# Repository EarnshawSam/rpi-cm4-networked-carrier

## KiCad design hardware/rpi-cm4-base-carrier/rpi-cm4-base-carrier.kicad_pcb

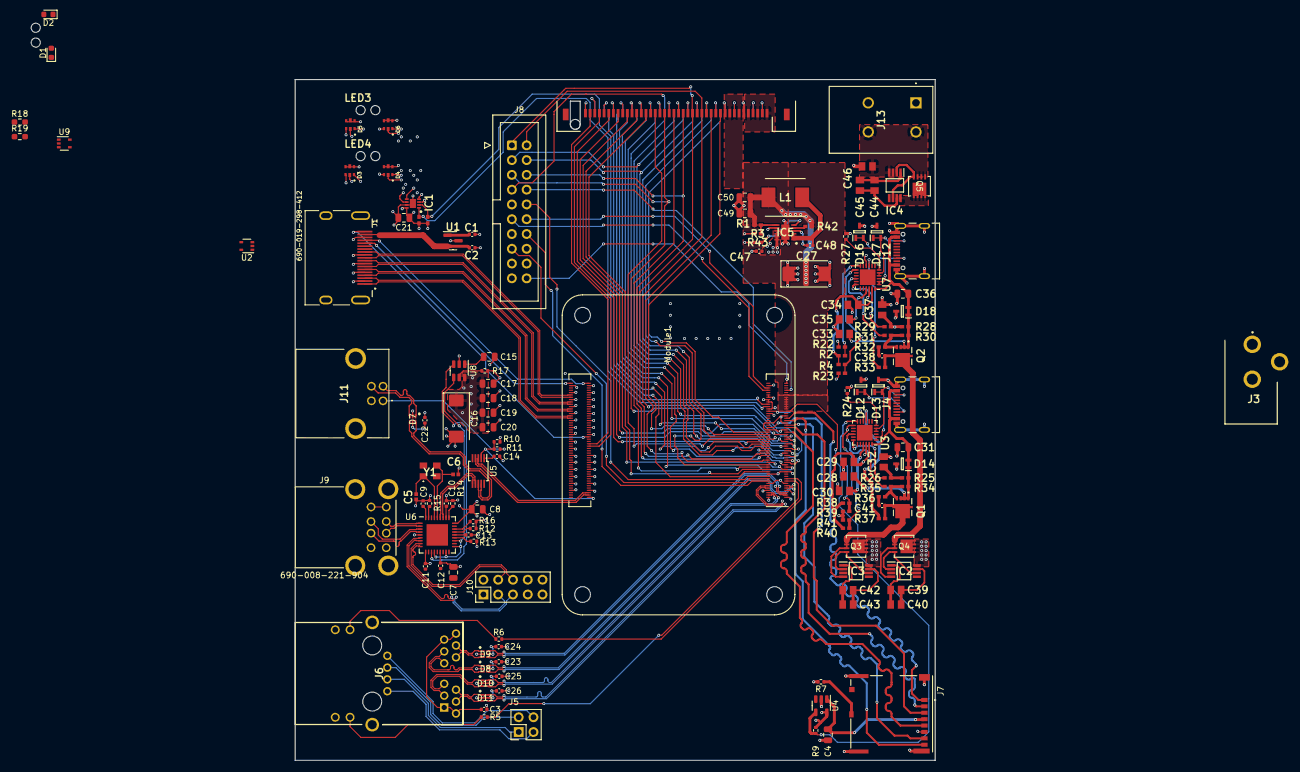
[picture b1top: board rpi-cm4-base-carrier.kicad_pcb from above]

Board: 4 copper layers, 110.0 x 117.0 mm, 148 parts (1 on the bottom side), 168 nets.

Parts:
C1, C2, C3, C9, C10, C11, C12, C13, C14, C22, C23, C24, C25, C26, C38, C41, C47, C48: 100n; C_0402_1005Metric
C4, C7, C8, C15, C17, C18, C19, C20, C21, C31, C36, C49, C50: 10u; C_0805_2012Metric
C5, C6: 8pf; CAPC1005X56N
C16, C27: 100uF; CP_EIA-7343-31_Kemet-D
C28, C29, C30, C32, C33, C34, C35, C37, C39, C40, C42, C43, C44, C45, C46: 1u; RESC2012X140N
D1: LED Green; LED_0603_1608Metric
D2: LED Red; LED_0603_1608Metric
D3, D4, D5, D6: 19-337C_RSBHGHC-A88_4T; LED_19-337C_RSBHGHC-A88_4T
D7, D8, D9, D10, D11: USBULC6-2M6; SON50P100X145X60-6N-D
D12, D13, D14, D16, D17, D18: ESDA25W; SOT65P210X110-3N
IC1: KTD2052BEVAA-TR; SON50P200X200X58-9N
IC2, IC3, IC4: LM74610QDGKRQ1; SOP65P490X110-8N
IC5: LMR51450FNDRRR; SON50P300X300X80-13N-D
J1: 690-019-298-412; EDAC 690-019-298-412
J2: ERM8-040-01-X-D-EM2-L-XX; SAMTEC_ERM8-040-01-X-D-EM2-L-XX
J3: PJ-102BH; PJ-102AH
J4, J12: USB4105-GF-A; GCT_USB4105-GF-A
J5: THD-02-R; PinHeader_2x02_P2.54mm_Vertical
J6: JT4-1202HL; JT41202HL
J7: Micro_SD_Card_Det; SDCARD_MOLEX_503398-1892
J8: Conn_02x10_Odd_Even; IDC-Header_2x10_P2.54mm_Vertical
J9: 690-008-221-904; MOLEX_USB_67298-4090
J10: Conn_02x05_Odd_Even; PinHeader_2x05_P2.54mm_Vertical
J11: XM7B-0442; XM7B0442
J13: 1190297
L1: IHLP2525EZER2R2M01-2.2uH; INDPM6965X500N
LED1, LED2, LED3, LED4: 515-1114F
Module1: ComputeModule4-CM4; Raspberry-Pi-4-Compute-Module
Q1, Q2: STL6P3LLH6; TRANS_STL6P3LLH6
Q3, Q4, Q5: STL11N3LLH6; POWERFLAT_3P3X3P3_STM
R1, R30, R34, R42: 100K; RESC1005X40N
R2, R4, R38, R41: NF; RESC1005X40N
R3: 19K1; RESC1005X40N
R5, R6: 470R; R_0402_1005Metric
R7: nf; R_0402_1005Metric
R9, R15, R24, R27: 12K 1%; R_0402_1005Metric
R10, R11: 2.2K 1%; R_0402_1005Metric
R12, R13, R14, R16: 36K 1%; R_0402_1005Metric
R17: 15K 1%; R_0402_1005Metric
R18, R19: 1k; R_0603_1608Metric_Pad0.98x0.95mm_HandSolder
R20, R21: 4K7; RESC1005X37N
R22, R23, R31, R35, R39, R40: 22K; RESC1005X40N
R25, R28: 470R; RESC1005X40N
R26, R29, R33, R37: 1k; RESC1005X37N
R32, R36: 100R; RESC1005X40N
R43: 13K3; RESC1005X40N
U1: RT9742SNGV; SOT-23
U2, U9: 74LVC1G07SE-7; SOT-353_SC-70-5
U3, U7: STUSB4500QTR; QFN-24-1EP_4x4mm_P0.5mm_EP2.7x2.7mm
U4: RT9742GGJ5; SOT-23-5
U5: FSUSB42MUX; MSOP-10_3x3mm_P0.5mm
U6: USB2514B-I/M2; QFN-36-1EP_6x6mm_P0.5mm_EP3.7x3.7mm
U8: AP22653W6; SOT-23-6
Y1: CX3225CA24000D0HSSCC

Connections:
+1V8: Module1.88 (+1.8v_(Output)), Module1.90 (+1.8v_(Output))
+3V3: C7.1, C8.1, C9.1, C10.1, C11.1, C12.1, C13.1, C14.1, C21.1, D1.2 (A), D2.2 (A), IC1.8 (VIN), J2.63, J2.67, J6.18 (A_YELLOW), J6.20 (A_GREEN), Module1.78 (GPIO_VREF(1.8v/3.3v_Input)), Module1.84 (+3.3v_(Output)), Module1.86 (+3.3v_(Output)), R7.1, R9.1, R20.2, R21.2, U4.5 (IN), U5.1 (VCC), U6.5 (VDDA33), U6.10 (VDDA33), U6.15 (VDD33), U6.23 (VDD33), U6.27 (VBUS_DET), U6.29 (VDDA33), U6.36 (VDDA33), U9.5 (VCC)
+5V: C1.1, C15.1, C49.1, C50.1, J2.64, J2.68, L1.2, Module1.77 (+5v_(Input)), Module1.79 (+5v_(Input)), Module1.81 (+5v_(Input)), Module1.83 (+5v_(Input)), Module1.85 (+5v_(Input)), Module1.87 (+5v_(Input)), R1.1, R42.1, U1.1 (IN), U2.5 (VCC), U8.1 (IN)
+20V: C27.1, C47.1, IC2.8 (CATHODE), IC3.8 (CATHODE), IC4.8 (CATHODE), IC5.9 (EN), IC5.10 (VIN_1), IC5.11 (VIN_2), IC5.12 (VIN_3), J2.71, J2.72, J2.75, J2.76, J2.79, J2.80, Q3.5, Q3.6, Q3.7, Q3.8, Q4.5, Q4.6, Q4.7, Q4.8, Q5.5, Q5.6, Q5.7, Q5.8
/Board_Edge_Connector/AIN0: J8.11, Module1.94 (AnalogIP0)
/Board_Edge_Connector/AIN1: J8.12, Module1.96 (AnalogIP1)
/Board_Edge_Connector/EEPROM_nWP: J8.10, Module1.20 (EEPROM_nWP)
/Board_Edge_Connector/GLOBAL_EN: J8.20, Module1.99 (Global_EN)
/Board_Edge_Connector/GPIO2: J2.59, Module1.58 (GPIO2)
/Board_Edge_Connector/GPIO3: J2.60, Module1.56 (GPIO3)
/Board_Edge_Connector/GPIO4: J2.55, Module1.54 (GPIO4)
/Board_Edge_Connector/GPIO5: J2.56, Module1.34 (GPIO5)
/Board_Edge_Connector/GPIO6: J2.51, Module1.30 (GPIO6)
/Board_Edge_Connector/GPIO7: J2.52, J8.2, Module1.37 (GPIO7)
/Board_Edge_Connector/GPIO8: J2.47, J8.4, Module1.39 (GPIO8)
/Board_Edge_Connector/GPIO9: J2.48, J8.1, Module1.40 (GPIO9)
/Board_Edge_Connector/GPIO10: J2.43, J8.3, Module1.44 (GPIO10)
/Board_Edge_Connector/GPIO11: J2.44, J8.6, Module1.38 (GPIO11)
/Board_Edge_Connector/GPIO12: J2.39, Module1.31 (GPIO12)
/Board_Edge_Connector/GPIO13: J2.40, Module1.28 (GPIO13)
/Board_Edge_Connector/GPIO14: J2.35, J8.7, Module1.55 (GPIO14)
/Board_Edge_Connector/GPIO15: J2.36, J8.5, Module1.51 (GPIO15)
/Board_Edge_Connector/GPIO16: J2.31, Module1.29 (GPIO16)
/Board_Edge_Connector/GPIO17: J2.32, Module1.50 (GPIO17)
/Board_Edge_Connector/GPIO18: J2.27, Module1.49 (GPIO18)
/Board_Edge_Connector/GPIO19: J2.28, Module1.26 (GPIO19)
/Board_Edge_Connector/GPIO20: J2.23, Module1.27 (GPIO20)
/Board_Edge_Connector/GPIO21: J2.24, Module1.25 (GPIO21)
/Board_Edge_Connector/GPIO22: J2.19, Module1.46 (GPIO22)
/Board_Edge_Connector/GPIO23: J2.20, Module1.47 (GPIO23)
/Board_Edge_Connector/GPIO24: J2.15, Module1.45 (GPIO24)
/Board_Edge_Connector/GPIO25: J2.16, Module1.41 (GPIO25)
/Board_Edge_Connector/GPIO26: J2.11, Module1.24 (GPIO26)
/Board_Edge_Connector/GPIO27: J2.12, Module1.48 (GPIO27)
/Board_Edge_Connector/HDMI1_SCL: J2.04, Module1.147 (HDMI1_SCL)
/Board_Edge_Connector/HDMI1_SDA: J2.08, Module1.145 (HDMI1_SDA)
/Board_Edge_Connector/RUN_PG: Module1.92 (RUN_PG), U2.2
/Board_Edge_Connector/SYNC_IN: J8.14, Module1.16 (Ethernet_SYNC_IN(1.8v))
/Board_Edge_Connector/SYNC_OUT: J8.15, Module1.18 (Ethernet_SYNC_OUT(1.8v))
/Board_Edge_Connector/nRPIBOOT: J8.8, Module1.93 (nRPIBOOT)
/CM4 GPIO/ETH_LEDG: Module1.17 (Ethernet_nLED2(3.3v)), R6.2
/CM4 GPIO/ETH_LEDY: Module1.15 (Ethernet_nLED3(3.3v)), R5.2
/CM4 GPIO/LEDs/RGB1: D3.5, D4.3, D5.1, D6.2, D6.4, D6.6, IC1.6 (LED1)
/CM4 GPIO/LEDs/RGB2: D3.3, D4.1, D5.2, D5.4, D5.6, D6.5, IC1.5 (LED2)
/CM4 GPIO/LEDs/RGB3: D3.1, D4.2, D4.4, D4.6, D5.5, D6.3, IC1.3 (LED4)
/CM4 GPIO/LEDs/RGB4: D3.2, D3.4, D3.6, D4.5, D5.3, D6.1, IC1.4 (LED3)
/CM4 GPIO/SCL0: IC1.1 (SCL), J2.03, Module1.80 (SCL0), R20.1, U3.7 (SCL), U7.7 (SCL)
/CM4 GPIO/SDA0: IC1.2 (SDA), J2.07, Module1.82 (SDA0), R21.1, U3.8 (SDA), U7.8 (SDA)
/CM4 GPIO/SD_CLK: J7.5 (CLK), Module1.57 (SD_CLK)
/CM4 GPIO/SD_CMD: J7.3 (CMD), Module1.62 (SD_CMD)
/CM4 GPIO/SD_DAT0: J7.7 (DAT0), Module1.63 (SD_DAT0)
/CM4 GPIO/SD_DAT1: J7.8 (DAT1), Module1.67 (SD_DAT1)
/CM4 GPIO/SD_DAT2: J7.1 (DAT2), Module1.69 (SD_DAT2)
/CM4 GPIO/SD_DAT3: J7.2 (DAT3/CD), Module1.61 (SD_DAT3)
/CM4 GPIO/SD_PWR_ON: Module1.75 (SD_PWR_ON), R9.2, U4.4 (EN)
/CM4 GPIO/TRD0_N: D11.1 (D+), D11.6 (I/O1), J6.9 (TRD1-), Module1.10 (Ethernet_Pair0_N)
/CM4 GPIO/TRD0_P: D11.3 (D-), D11.4 (I/O2), J6.8 (TRD1+), Module1.12 (Ethernet_Pair0_P)
/CM4 GPIO/TRD1_N: D10.3 (D-), D10.4 (I/O2), J6.3 (TRD2-), Module1.6 (Ethernet_Pair1_N)
/CM4 GPIO/TRD1_P: D10.1 (D+), D10.6 (I/O1), J6.2 (TRD2+), Module1.4 (Ethernet_Pair1_P)
/CM4 GPIO/TRD2_N: D8.3 (D-), D8.4 (I/O2), J6.5 (TRD3-), Module1.9 (Ethernet_Pair2_N)
/CM4 GPIO/TRD2_P: D8.1 (D+), D8.6 (I/O1), J6.4 (TRD3+), Module1.11 (Ethernet_Pair2_P)
/CM4 GPIO/TRD3_N: D9.1 (D+), D9.6 (I/O1), J6.11 (TRD4-), Module1.5 (Ethernet_Pair3_N)
/CM4 GPIO/TRD3_P: D9.3 (D-), D9.4 (I/O2), J6.10 (TRD4+), Module1.3 (Ethernet_Pair3_P)
/CM4 GPIO/nLED_Activity: Module1.21 (PI_nLED_Activity), R18.2
/CM4 GPIO/nPWR_LED: Module1.95 (nPI_LED_PWR), U9.2
/CM4 High Speed/HDMI0_CK_N: J1.12 (CK-), Module1.190 (HDMI0_CLK_N)
/CM4 High Speed/HDMI0_CK_P: J1.10 (CK+), Module1.188 (HDMI0_CLK_P)
/CM4 High Speed/HDMI0_D0_N: J1.9 (D0-), Module1.184 (HDMI0_TX0_N)
/CM4 High Speed/HDMI0_D0_P: J1.7 (D0+), Module1.182 (HDMI0_TX0_P)
/CM4 High Speed/HDMI0_D1_N: J1.6 (D1-), Module1.178 (HDMI0_TX1_N)
/CM4 High Speed/HDMI0_D1_P: J1.4 (D1+), Module1.176 (HDMI0_TX1_P)
/CM4 High Speed/HDMI0_D2_N: J1.3 (D2-), Module1.172 (HDMI0_TX2_N)
/CM4 High Speed/HDMI0_D2_P: J1.1 (D2+), Module1.170 (HDMI0_TX2_P)
/CM4 High Speed/HDMI0_HOTPLUG: J1.19 (HPD/HEAC-), Module1.153 (HDMI0_HOTPLUG)
/CM4 High Speed/HDMI0_SCL: J1.15 (SCL), Module1.200 (HDMI0_SCL)
/CM4 High Speed/HDMI0_SDA: J1.16 (SDA), Module1.199 (HDMI0_SDA)
/CM4 High Speed/HDMI/HDMI_5v: C2.1, J1.18 (+5V), U1.2 (OUT)
/CM4 High Speed/USB2-HUB/HD1_N: J9.2 (D-`), U6.1 (USBDM_DN1/PRT_DIS_M1)
/CM4 High Speed/USB2-HUB/HD1_P: J9.3 (D+`), U6.2 (USBDP_DN1/PRT_DIS_P1)
/CM4 High Speed/USB2-HUB/HD2_N: J9.6 (D-), U6.3 (USBDM_DN2/PRT_DIS_M2)
/CM4 High Speed/USB2-HUB/HD2_P: J9.7 (D+), U6.4 (USBDP_DN2/PRT_DIS_P2)
/CM4 High Speed/USB2-HUB/HD3_N: J10.3, U6.6 (USBDM_DN3/PRT_DIS_M3)
/CM4 High Speed/USB2-HUB/HD3_P: J10.5, U6.7 (USBDP_DN3/PRT_DIS_P3)
/CM4 High Speed/USB2-HUB/HD4_N: J10.4, U6.8 (USBDM_DN4/PRT_DIS_M4)
/CM4 High Speed/USB2-HUB/HD4_P: J10.6, U6.9 (USBDP_DN4/PRT_DIS_P4)
/CM4 High Speed/USB2-HUB/PWR1: U6.12 (PRTPWR1/BC_EN1), U8.3 (EN)
/CM4 High Speed/USB2-HUB/USBD_N: D7.1 (D+), D7.6 (I/O1), J11.2, U5.8 (HSD1_M)
/CM4 High Speed/USB2-HUB/USBH_N: U5.6 (HSD0_M), U6.30 (USBDM_UP)
/CM4 High Speed/USB2-HUB/USBH_P: U5.7 (HSD0_P), U6.31 (USBDP_UP)
/CM4 High Speed/USB2-HUB/VBUS: C16.1, C17.1, C18.1, C19.1, C20.1, J9.1 (VBUS`), J9.5 (VBUS), J10.1, J10.2, U8.6 (OUT)
/CM4 High Speed/USB2-HUB/nEXTRST: Module1.100 (nEXTRST), U6.26 (RESET_N)
/CM4 High Speed/USB2-HUB/nOCS1: U6.13 (OCS_N1), U6.17 (OCS_N2), U6.19 (OCS_N3), U6.21 (OCS_N4), U8.4 (nFault)
/CM4 High Speed/USB2_N: Module1.103 (USB2_N), U5.4 (D_N)
/CM4 High Speed/USB2_P: Module1.105 (USB2_P), U5.3 (D_P)
/CM4 High Speed/USB_OTG_ID: Module1.101 (USB_OTG_ID), R10.1, R11.2, U5.2 (SEL)
/Power_Input/AUX_20V: C46.1, IC4.4 (ANODE), J3.1, J13.3 (2.1), J13.4 (2.2), Q5.1, Q5.2, Q5.3
/Power_Input/USBC_PWR.Sheet1/+2V7: C29.1, R38.1, R40.1, U3.23 (VREG_2V7)
/Power_Input/USBC_PWR.Sheet1/ADDR0: R38.2, R39.1, U3.12 (ADDR0)
/Power_Input/USBC_PWR.Sheet1/ADDR1: R40.2, R41.1, U3.13 (ADDR1)
/Power_Input/USBC_PWR.Sheet1/CC1: D12.1 (CATHODE_1), D12.2 (CATHODE_2), J4.A5 (CC1), U3.1 (CC1DB), U3.2 (CC1)
/Power_Input/USBC_PWR.Sheet1/CC2: D13.1 (CATHODE_1), D13.2 (CATHODE_2), J4.B5 (CC2), U3.4 (CC2), U3.5 (CC2DB)
/Power_Input/USBC_PWR.Sheet1/V_SINK: C41.1, IC3.4 (ANODE), Q1.5_8 (5), Q3.1, Q3.2, Q3.3, R37.1
/Power_Input/USBC_PWR.Sheet/+2V7: C34.1, R2.1, R4.1, U7.23 (VREG_2V7)
/Power_Input/USBC_PWR.Sheet/ADDR0: R2.2, R22.1, U7.12 (ADDR0)
/Power_Input/USBC_PWR.Sheet/ADDR1: R4.2, R23.1, U7.13 (ADDR1)
/Power_Input/USBC_PWR.Sheet/CC1: D16.1 (CATHODE_1), D16.2 (CATHODE_2), J12.A5 (CC1), U7.1 (CC1DB), U7.2 (CC1)
/Power_Input/USBC_PWR.Sheet/CC2: D17.1 (CATHODE_1), D17.2 (CATHODE_2), J12.B5 (CC2), U7.4 (CC2), U7.5 (CC2DB)
/Power_Input/USBC_PWR.Sheet/V_SINK: C38.1, IC2.4 (ANODE), Q2.5_8 (5), Q4.1, Q4.2, Q4.3, R33.1
/SDCard/SD_PWR: C4.1, J7.4 (VDD), U4.1 (OUT)
/magjack/TR0_TAP: J5.3, J6.13 (TRP1)
/magjack/TR1_TAP: J5.1, J6.14 (TRP2)
/magjack/TR2_TAP: J5.2, J6.15 (TRP3)
/magjack/TR3_TAP: J5.4, J6.16 (TRP4)
/magjack/TRCT: C3.1, J6.1 (TRCT2), J6.6 (TRCT3), J6.7 (TRCT1), J6.12 (TRCT4)
GND: C1.2, C2.2, C3.2, C4.2, C5.2, C6.2, C7.2, C8.2, C9.2, C10.2, C11.2, C12.2, C13.2, C14.2, C15.2, C16.2, C17.2, C18.2, C19.2, C20.2, C21.2, C22.2, C23.2, C24.2, C25.2, C26.2, C27.2, C28.2, C29.2, C30.2, C31.2, C32.2, C33.2, C34.2, C35.2, C36.2, C37.2, C46.2, C47.2, C49.2, C50.2, D7.2 (GND_1), D7.4 (I/O2), D8.2 (GND_1), D9.2 (GND_1), D10.2 (GND_1), D11.2 (GND_1), D12.3 (ANODE), D13.3 (ANODE), D14.3 (ANODE), D16.3 (ANODE), D17.3 (ANODE), D18.3 (ANODE), IC1.7 (GND), IC1.9 (EP), IC5.8 (AGND), IC5.13 (PGND/DAP), J1.2 (D2S), J1.5 (D1S), J1.8 (D0S), J1.11 (CKS), J1.17 (GND), J1.SH1 (SH), J1.SH2 (SH), J1.SH3 (SH), J1.SH4 (SH), J2.01, J2.02, J2.05, J2.06, J2.09, J2.10, J2.13, J2.14, J2.17, J2.18, J2.21, J2.22, J2.25, J2.26, J2.29, J2.30, J2.33, J2.34, J2.37, J2.38, J2.41, J2.42, J2.45, J2.46, J2.49, J2.50, J2.53, J2.54, J2.57, J2.58, J2.61, J2.62, J2.65, J2.66, J2.69, J2.70, J2.73, J2.74, J2.77, J2.78, J3.2, J3.3, J4.A1/B12 (GND), J4.B1/A12 (GND), J4.G1 (GND), J4.G2 (GND), J4.G3 (GND), J4.G4 (GND), J6.MH3, J6.MH4, J7.6 (VSS), J7.11 (SHIELD), J8.9, J8.13, J8.16, J8.17, J8.18, J9.4 (GND`), J9.8 (GND), J9.MT1, J9.MT2, J9.MT3, J9.MT4, J10.7, J10.8, J11.3, J11.MH1, J11.MH2, J12.A1/B12 (GND), J12.B1/A12 (GND), J12.G1 (GND), J12.G2 (GND), J12.G3 (GND), J12.G4 (GND), J13.1 (1.1), J13.2 (1.2), Module1.1 (GND), Module1.2 (GND), Module1.7 (GND), Module1.8 (GND), Module1.13 (GND), Module1.14 (GND), Module1.22 (GND), Module1.23 (GND), Module1.32 (GND), Module1.33 (GND), Module1.42 (GND), Module1.43 (GND), Module1.52 (GND), Module1.53 (GND), Module1.59 (GND), Module1.60 (GND), Module1.65 (GND), Module1.66 (GND), Module1.71 (GND), Module1.74 (GND), Module1.98 (GND), Module1.107 (GND), Module1.108 (GND), Module1.113 (GND), Module1.114 (GND), Module1.119 (GND), Module1.120 (GND), Module1.125 (GND), Module1.126 (GND), Module1.131 (GND), Module1.132 (GND), Module1.137 (GND), Module1.138 (GND), Module1.144 (GND), Module1.150 (GND), Module1.155 (GND), Module1.156 (GND), Module1.161 (GND), Module1.162 (GND), Module1.167 (GND), Module1.168 (GND), Module1.173 (GND), Module1.174 (GND), Module1.179 (GND), Module1.180 (GND), Module1.185 (GND), Module1.186 (GND), Module1.191 (GND), Module1.192 (GND), Module1.197 (GND), Module1.198 (GND), R3.1, R10.2, R12.2, R13.2, R14.2, R15.1, R16.2, R17.2, R22.2, R23.2, R24.1, R27.1, R39.2, R41.2, R43.1, U1.3 (GND), U2.3 (GND), U3.10 (GND), U3.22 (VSYS), U3.25 (GND), U4.2 (GND), U5.5 (GND), U5.9 (HSD1_P), U5.10 (nOE), U6.37 (VSS), U7.10 (GND), U7.22 (VSYS), U7.25 (GND), U8.2 (GND), U9.3 (GND)
unnamed: C32.1, R25.2, R26.1
unnamed: C37.1, R28.2, R29.1
unnamed: C38.2, R32.2
unnamed: C41.2, R36.2
unnamed: D1.1 (K), R18.1
unnamed: D2.1 (K), R19.1
unnamed: C22.1, D7.5 (GND_2)
unnamed: C23.1, D8.5 (GND_2)
unnamed: C24.1, D9.5 (GND_2)
unnamed: C25.1, D10.5 (GND_2)
unnamed: C26.1, D11.5 (GND_2)
unnamed: C28.1, C31.1, D14.1 (CATHODE_1), D14.2 (CATHODE_2), J4.A4/B9 (VBUS), J4.B4/A9 (VBUS), Q1.1, Q1.2, Q1.3, R25.1, R34.1, U3.24 (VDD)
unnamed: C33.1, C36.1, D18.1 (CATHODE_1), D18.2 (CATHODE_2), J12.A4/B9 (VBUS), J12.B4/A9 (VBUS), Q2.1, Q2.2, Q2.3, R28.1, R30.1, U7.24 (VDD)
unnamed: IC2.2 (GATE_PULL_DOWN), IC2.6 (GATE_DRIVE), Q4.4
unnamed: C39.2, C40.2, IC2.7 (VCAPH)
unnamed: C39.1, C40.1, IC2.1 (VCAPL)
unnamed: IC3.2 (GATE_PULL_DOWN), IC3.6 (GATE_DRIVE), Q3.4
unnamed: C42.2, C43.2, IC3.7 (VCAPH)
unnamed: C42.1, C43.1, IC3.1 (VCAPL)
unnamed: IC4.2 (GATE_PULL_DOWN), IC4.6 (GATE_DRIVE), Q5.4
unnamed: C44.2, C45.2, IC4.7 (VCAPH)
unnamed: C44.1, C45.1, IC4.1 (VCAPL)
unnamed: C48.1, IC5.4 (BOOT)
unnamed: IC5.7 (FB), R1.2, R3.2
unnamed: IC5.5 (PG), R42.2
unnamed: IC5.6 (RT), R43.2
unnamed: C48.2, IC5.1 (SW_1), IC5.2 (SW_2), IC5.3 (SW_3), L1.1
unnamed: J6.19 (K_GREEN), R6.1
unnamed: J6.17 (K_YELLOW), R5.1
unnamed: J7.10 (DET_A), R7.2
unnamed: J8.19, U2.4
unnamed: J11.1, R11.1
unnamed: Q1.4, R34.2, R35.1, R36.1
unnamed: Q2.4, R30.2, R31.1, R32.1
unnamed: R19.2, U9.4
unnamed: R37.2, U3.9 (DISCH)
unnamed: R24.2, U3.6 (RESET)
unnamed: R35.2, U3.16 (VBUS_EN_SNK)
unnamed: R26.2, U3.18 (VBUS_VS_DISCH)
unnamed: C30.1, U3.21 (VREG_1V2)
unnamed: R16.1, U6.25 (HS_IND/CFG_SEL1)
unnamed: R15.2, U6.35 (RBIAS)
unnamed: R12.1, U6.24 (SCL/SMBCLK/CFG_SEL0)
unnamed: R13.1, U6.22 (SDA/SMBDATA/NON_REM1)
unnamed: R14.1, U6.28 (SUSP_IND/LOCAL_PWR/NON_REM0)
unnamed: C5.1, U6.33 (XTALIN/CLKIN), Y1.1 (HOT_1)
unnamed: C6.1, U6.32 (XTALOUT), Y1.3 (HOT_2)
unnamed: R33.2, U7.9 (DISCH)
unnamed: R27.2, U7.6 (RESET)
unnamed: R31.2, U7.16 (VBUS_EN_SNK)
unnamed: R29.2, U7.18 (VBUS_VS_DISCH)
unnamed: C35.1, U7.21 (VREG_1V2)
unnamed: R17.1, U8.5 (ILIM)

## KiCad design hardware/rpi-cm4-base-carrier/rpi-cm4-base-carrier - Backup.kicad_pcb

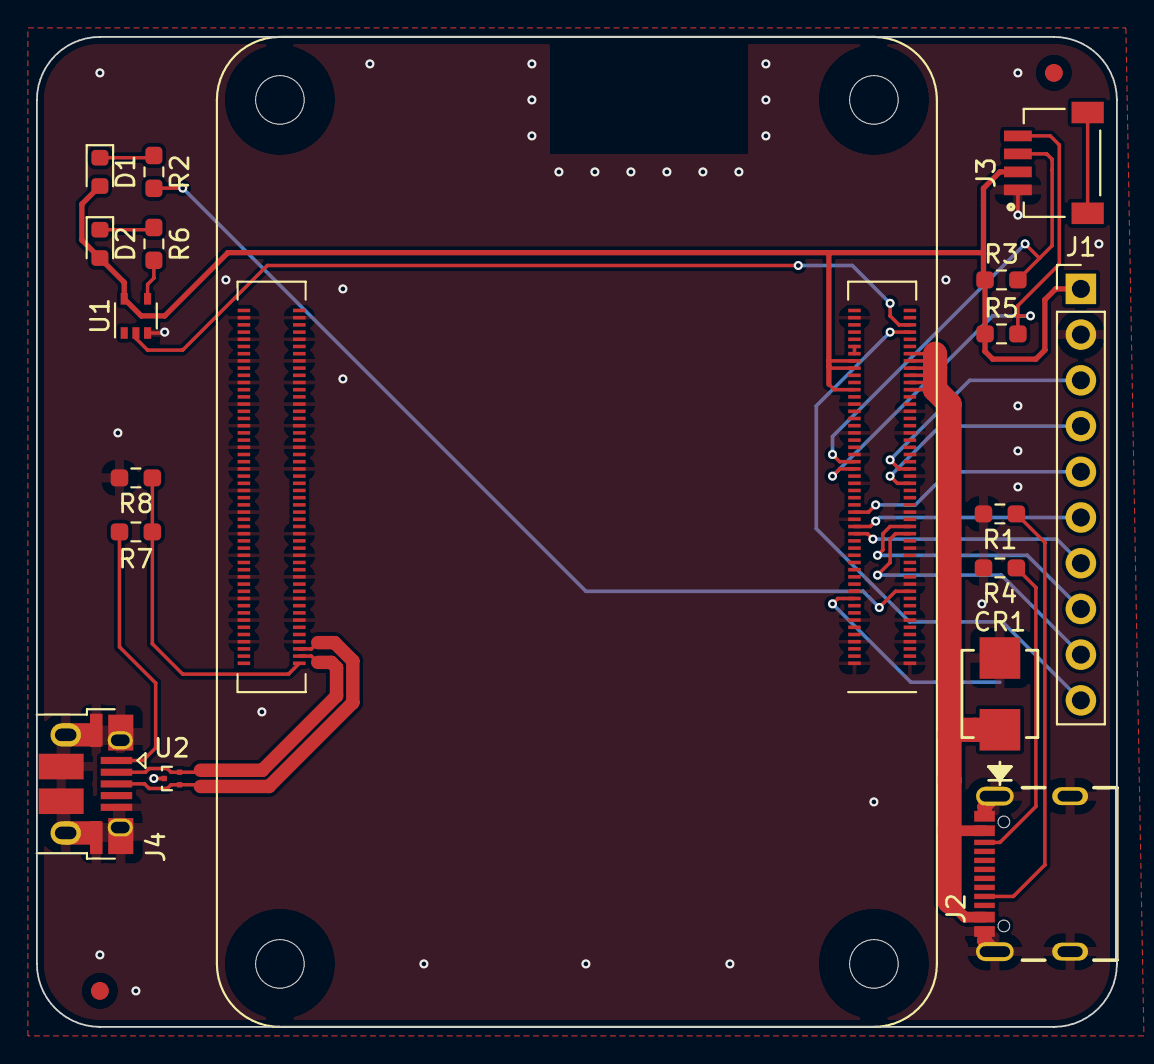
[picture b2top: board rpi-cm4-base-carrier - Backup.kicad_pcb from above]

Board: 2 copper layers, 60.0 x 55.0 mm, 19 parts (1 on the bottom side), 27 nets.

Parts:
CR1: SMBJ5.0A-TR
D1: LED Green; LED_0603_1608Metric
D2: LED Red; LED_0603_1608Metric
J1: DNP; PinHeader_1x10_P2.54mm_Vertical
J2: USB4105-GF-A; GCT_USB4105-GF-A
J3: SM04B-SRSS-TB(LF)(SN); JST_SM04B-SRSS-TB(LF)(SN)
J4: USB_OTG; USB_Micro-B_EDAC_UCON00686
JP1: SolderJumper_2_Open; SolderJumper-2_P1.3mm_Open_RoundedPad1.0x1.5mm
Module1: ComputeModule4-CM4; Raspberry-Pi-4-Compute-Module
R1, R4: 5.1k; R_0603_1608Metric_Pad0.98x0.95mm_HandSolder
R2, R6: 1k; R_0603_1608Metric_Pad0.98x0.95mm_HandSolder
R3, R5: DNP; R_0603_1608Metric_Pad0.98x0.95mm_HandSolder
R7, R8: 2.2K 1%; R_0603_1608Metric_Pad0.98x0.95mm_HandSolder
U1: 74LVC1G07SE-7; SOT-353_SC-70-5
U2: TPD2EUSB30; Texas_DRT-3

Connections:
+1.8V: Module1.88 (+1.8v_(Output)), Module1.90 (+1.8v_(Output))
+3.3V: D1.2 (A), D2.2 (A), J1.1, J3.2, Module1.78 (GPIO_VREF(1.8v/3.3v_Input)), Module1.84 (+3.3v_(Output)), Module1.86 (+3.3v_(Output)), R3.1, R5.1, U1.5 (VCC)
+5V: CR1.1, J2.A4/B9 (VBUS), J2.B4/A9 (VBUS), Module1.77 (+5v_(Input)), Module1.79 (+5v_(Input)), Module1.81 (+5v_(Input)), Module1.83 (+5v_(Input)), Module1.85 (+5v_(Input)), Module1.87 (+5v_(Input))
/CM4 GPIO/EEPROM_nWP: JP1.1 (A), Module1.20 (EEPROM_nWP)
/CM4 GPIO/GPIO2: J3.3, Module1.58 (GPIO2), R3.2
/CM4 GPIO/GPIO3: J3.4, Module1.56 (GPIO3), R5.2
/CM4 GPIO/GPIO7: J1.9, Module1.37 (GPIO7)
/CM4 GPIO/GPIO8: J1.8, Module1.39 (GPIO8)
/CM4 GPIO/GPIO9: J1.6, Module1.40 (GPIO9)
/CM4 GPIO/GPIO10: J1.5, Module1.44 (GPIO10)
/CM4 GPIO/GPIO11: J1.7, Module1.38 (GPIO11)
/CM4 GPIO/GPIO14: J1.3, Module1.55 (GPIO14)
/CM4 GPIO/GPIO15: J1.4, Module1.51 (GPIO15)
/CM4 GPIO/nLED_Activity: Module1.21 (PI_nLED_Activity), R2.2
/CM4 GPIO/nPWR_LED: Module1.95 (nPI_LED_PWR), U1.2
/CM4 GPIO/nRPIBOOT: J1.10, Module1.93 (nRPIBOOT)
/CM4 High Speed/USB2_N: J4.2 (D-), Module1.103 (USB2_N), U2.2 (D-)
/CM4 High Speed/USB2_P: J4.3 (D+), Module1.105 (USB2_P), U2.1 (D+)
/CM4 High Speed/USB_OTG_ID: Module1.101 (USB_OTG_ID), R7.2, R8.1
GND: CR1.2, J1.2, J2.A1/B12 (GND), J2.B1/A12 (GND), J2.G1 (GND), J2.G2 (GND), J2.G3 (GND), J2.G4 (GND), J3.1, J4.5 (GND), J4.6 (Shield), JP1.2 (B), Module1.1 (GND), Module1.2 (GND), Module1.7 (GND), Module1.8 (GND), Module1.13 (GND), Module1.14 (GND), Module1.22 (GND), Module1.23 (GND), Module1.32 (GND), Module1.33 (GND), Module1.42 (GND), Module1.43 (GND), Module1.52 (GND), Module1.53 (GND), Module1.59 (GND), Module1.60 (GND), Module1.65 (GND), Module1.66 (GND), Module1.71 (GND), Module1.74 (GND), Module1.98 (GND), Module1.107 (GND), Module1.108 (GND), Module1.113 (GND), Module1.114 (GND), Module1.119 (GND), Module1.120 (GND), Module1.125 (GND), Module1.126 (GND), Module1.131 (GND), Module1.132 (GND), Module1.137 (GND), Module1.138 (GND), Module1.144 (GND), Module1.150 (GND), Module1.155 (GND), Module1.156 (GND), Module1.161 (GND), Module1.162 (GND), Module1.167 (GND), Module1.168 (GND), Module1.173 (GND), Module1.174 (GND), Module1.179 (GND), Module1.180 (GND), Module1.185 (GND), Module1.186 (GND), Module1.191 (GND), Module1.192 (GND), Module1.197 (GND), Module1.198 (GND), R1.2, R4.2, R8.2, U1.3 (GND), U2.3 (GND)
unnamed: D1.1 (K), R2.1
unnamed: D2.1 (K), R6.1
unnamed: J2.A5 (CC1), R1.1
unnamed: J2.B5 (CC2), R4.1
unnamed: J3.S1 (SHIELD), J3.S2 (SHIELD)
unnamed: J4.1 (VBUS), R7.1
unnamed: R6.2, U1.4

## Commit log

2024-01-13 schematic changes to add network, hdmi, usbhost and SD
2024-01-14 routing for some modules progressing quickly, USBHUB mostly complete, thought needed regarding which connectors should be exposed post assembly and which should be for internal use only. LED identifi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
2024-01-15 addition of 4xRGB LED's and I2C driver, also includes right angle lightpipe
2024-01-16 started final placement of blocks, realised ESD suppression devices cannot be manufactured with JLC, need to switch part
2024-01-19 started to route core connectors to CM4, RJ45 annoyingly has the inverse pinout to CM4, need to work out how to uncross tracking sensibly
2024-01-21 most diff pairs routed, forgot about intra-pair spacing
2024-01-22 schematic entry for samtec board edge connector complete, started breakout of GPIO lines for connection to board edge connector
2024-01-23 board edge connector mostly connected
2024-01-28 redundant USBC power schematic created, layout of single USBC input completed@
2024-01-29 PWR regs complete, EMI protection? LDO low noise passthrough??
2024-01-30 layout ready for review as major components now complete
2024-01-31 good routing and power plane progress, just some final plane progress remaining
2024-02-03 fan control added to sch, layout 90% complete, awaiting review
2024-02-03 convert IC refs to U refs and re-annotate, add fiducials and extra via stitching to layout
2024-02-07 design files exported ready for manufacture, LCSC part numbers added throughout the library
2024-02-12 files updated to kicad 8, 2x10 connector updated to correct origin
2024-02-13 moved edge samtec edge connector to correct positioning

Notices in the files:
hardware/rpi-cm4-base-carrier/rpi-cm4-base-carrier - Backup.kicad_pcb:
creativecommons.org/licenses/by/4.0
License: CC BY-SA 4.0
parts and their libraries:
Copyright 2016 Accelerated Designs. All rights reserved.
